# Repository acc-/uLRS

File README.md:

# μLRS
μLRS - micro LRS receiver, OpenLRSng compatible<br/>
RCGroups thread: http://www.rcgroups.com/forums/showthread.php?t=2371835

## License
<br />This work is licensed under a <a rel="license" href="http://creativecommons.org/licenses/by-nc-sa/4.0/">Creative Commons Attribution-NonCommercial-ShareAlike 4.0 International License</a>.

## General
μLRS boards are hardware compatible with OpenLRSng firmware for HW 8 (micro RX). Common features for μLRS boards are:
* input voltage 4-16V (max 3S lipo, 4S is too much voltage)
* PCB pads for 3.3v UART interface (RX, TX, DTR, GND) - do **NOT** try to use it with 5v uart interface
* analog RSSI output pad
* U.FL antenna connector
* RFM22b 100mW radio module
* LFCN-490 low pass filter (can be easily removed by replacing it with 1206 0R resistor)
* LC filter for radio power supply
* Atmega328P-MU microcontroller (QFN case)
* 0603 sized components - can be soldered at home (only atmega chip requires strong soldering skills)

## v2 board
Improved version of μLRS v1 with following changes:
* vias covered by soldermask (v1 has these with copper epxosed)
* removed I2C pads
* removed 3.3v pad
* removed resistors in TX/RX pads
* removed dedicated RESET pad (but still easily accessible at the most bottom-right capacitor pad)
* smaller board - 16x16mm (0.63" x 0.63"), exactly the same size as RFM22b module
* PCBs can be ordered here: https://oshpark.com/shared_projects/H6KfYEk2

## v2 BOM
* 4x 1k 0603 resistor
* 1x 10k 0603 resistor
* 2x 22p 0603 capacitor
* 4x 100nF 0603 capacitor
* 2x 1uF 0603 capacitor (on schema one is 0402, but 0603 fits perfectly and is easier to solder)
* 2x 10uF/6.3v 0603 tantalum capacitor
* 1x 47uF/16v SMD B tantalum capacitor (schema is for SMD A, but 16v SMD A cannot be found, you can use SMD-A 6.3v but then you are limited to 5v power supply)
* 1x SOT-323 Schottky diode (let it be around 200mA), for example BAT165
* 1x green 0603 led
* 1x red 0603 led
* 1x LFCN-490 filter
* 1x mcp1703cb SOT23 voltage regulator (supports max 16V)
* 1x 16MHz crystal oscillator 3525 case
* 1x 10uH 1210 inductor
* 1x Atmega328P-MU (MLF32 case) microcontroller
* 1x RFM22B-433-S2 radio module
* 1x U.FL antenna connector

## v1 board (deprecated)
μLRS v1 is a first prototype board:
* PCB dimensions: 20x18mm
* I2C interface (SDA, SCL) pads
* 3.3v pad
* RESET pad (for SPI programming)
* big 47uF tantalum capacitor for input voltage filtering
* two 10uF tantalum capacitors (one for 3.3v filtering, another one for RSSI analog output)
* can be used also as a **transmitter**
* PCBs can be ordered here: https://oshpark.com/shared_projects/nFa7UehY

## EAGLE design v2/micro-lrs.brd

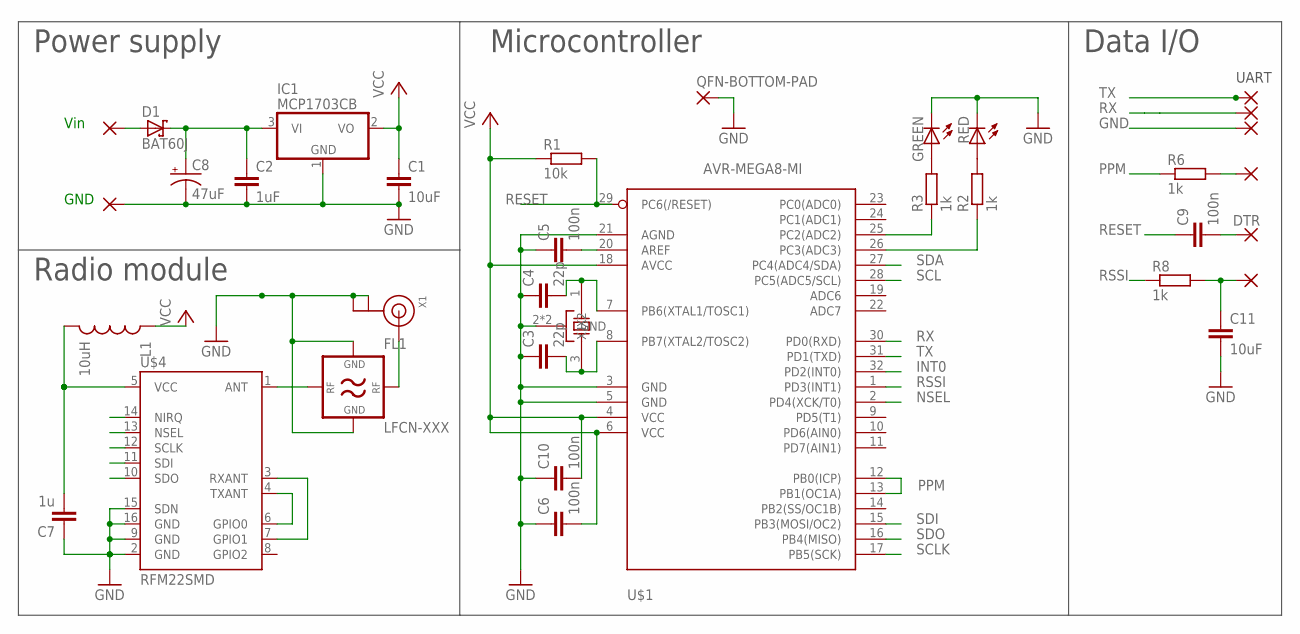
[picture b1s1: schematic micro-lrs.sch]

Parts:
+5V: SMD2; SMD1,27-2,54
C1, C11: 10uF; C0603
C2: 1uF; C0603
C3, C4: 22p; C0603K
C5, C6, C9, C10: 100n; C0603K
C7: 1u; C0402
C8: 47uF; EIA3216
D1: BAT60J; SOD323_ST
DTR: SMD2; SMD1,27-2,54
FL1: LFCN-XXX; FV1206
GND: SMD2; SMD1,27-2,54
IC1: MCP1703CB; SOT23
L1: 10uH; 1210
LED1: GREEN; CHIPLED_0603
LED2: RED; CHIPLED_0603
PPM: SMD2; SMD1,27-2,54
QFN-BOTTOM-PAD: QFN-PAD; SMD100X100
R1: 10k; R0603
R2, R3, R6, R8: 1k; R0603
RSSI: SMD2; SMD1,27-2,54
RX: SMD2; SMD1,27-2,54
TX: SMD2; SMD1,27-2,54
U$1: AVR-MEGA8-MI; MLF32
U$2: CTS_32X25_SMD; CTS_32X25
U$4: RFM22SMD; RFM22-XXX-S2
UART-GND: SMD2; SMD1,27-2,54
X1: ANTENNA_U.FL; U.FL

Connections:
ANT-PAD: FL1.1 (IO1), U$4.1 (ANT)
AREF: C5.2, U$1.20 (AREF)
DTR: C9.2, DTR.1
GND: C1.2, C2.2, C3.1, C4.1, C5.1, C6.1, C7.1, C8.C (-), C10.1, C11.2, FL1.3 (GND2), FL1.4 (GND1), GND.1, IC1.1 (GND), LED1.C, LED2.C, QFN-BOTTOM-PAD.P$2, U$1.3 (GND), U$1.5 (GND), U$1.21 (AGND), U$2.2 (GND), U$2.4 (GND), U$4.2 (GND), U$4.9 (GND), U$4.15 (SDN), U$4.16 (GND), UART-GND.1, X1.1 (GND), X1.2 (GND)
INT0: U$1.32 (PD2(INT0)), U$4.14 (NIRQ)
unnamed: C4.2, U$1.7 (PB6(XTAL1/TOSC1)), U$2.1 (X1)
unnamed: C3.2, U$1.8 (PB7(XTAL2/TOSC2)), U$2.3 (X2)
unnamed: R3.1, U$1.25 (PC2(ADC2))
unnamed: R2.1, U$1.26 (PC3(ADC3))
unnamed: LED1.A, R3.2
unnamed: LED2.A, R2.2
unnamed: FL1.2 (IO2), X1.3 (SIGNAL)
unnamed: U$4.4 (TXANT), U$4.6 (GPIO0)
unnamed: U$4.3 (RXANT), U$4.7 (GPIO1)
NSEL: U$1.2 (PD4(XCK/T0)), U$4.13 (NSEL)
PPM: R6.1, U$1.12 (PB0(ICP)), U$1.13 (PB1(OC1A))
PPMPAD: PPM.1, R6.2
RESET: C9.1, R1.2, U$1.29 (PC6(/RESET))
RSSI: R8.1, U$1.1 (PD3(INT1))
RSSIPAD: C11.1, R8.2, RSSI.1
RX: RX.1, U$1.30 (PD0(RXD))
SCL: U$1.28 (PC5(ADC5/SCL))
SCLK: U$1.17 (PB5(SCK)), U$4.12 (SCLK)
SDA: U$1.27 (PC4(ADC4/SDA))
SDI: U$1.15 (PB3(MOSI/OC2)), U$4.11 (SDI)
SDO: U$1.16 (PB4(MISO)), U$4.10 (SDO)
TX: TX.1, U$1.31 (PD1(TXD))
VCC: C1.1, C6.2, C10.2, IC1.2 (VO), L1.1, R1.1, U$1.4 (VCC), U$1.6 (VCC), U$1.18 (AVCC)
VCC-RADIO: C7.2, L1.2, U$4.5 (VCC)
VIN: C2.1, C8.A (+), D1.C, IC1.3 (VI)
VIN-BEFORE-DIODE: +5V.1, D1.A

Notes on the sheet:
Power supply
Data I/O
Microcontroller
Radio module
UART
Vin
GND

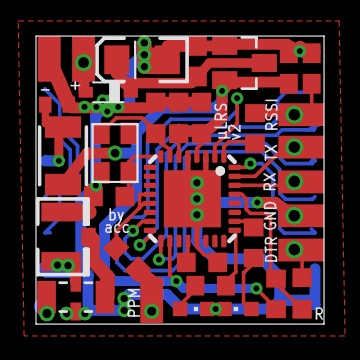
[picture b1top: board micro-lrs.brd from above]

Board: 2 copper layers, 16.0 x 16.0 mm, 35 parts (1 on the bottom side), 29 nets.

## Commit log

2015-05-01 initial import
2015-05-31 v2 sources
2015-05-31 updated documentation

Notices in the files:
parts and their libraries:
SparkFun-RF: Licensing: Creative Commons ShareAlike 4.0 International - https://creativecommons.org/licenses/by-sa/4.0
mini-circuits: Copyright (C) 2013, Bob Starr
